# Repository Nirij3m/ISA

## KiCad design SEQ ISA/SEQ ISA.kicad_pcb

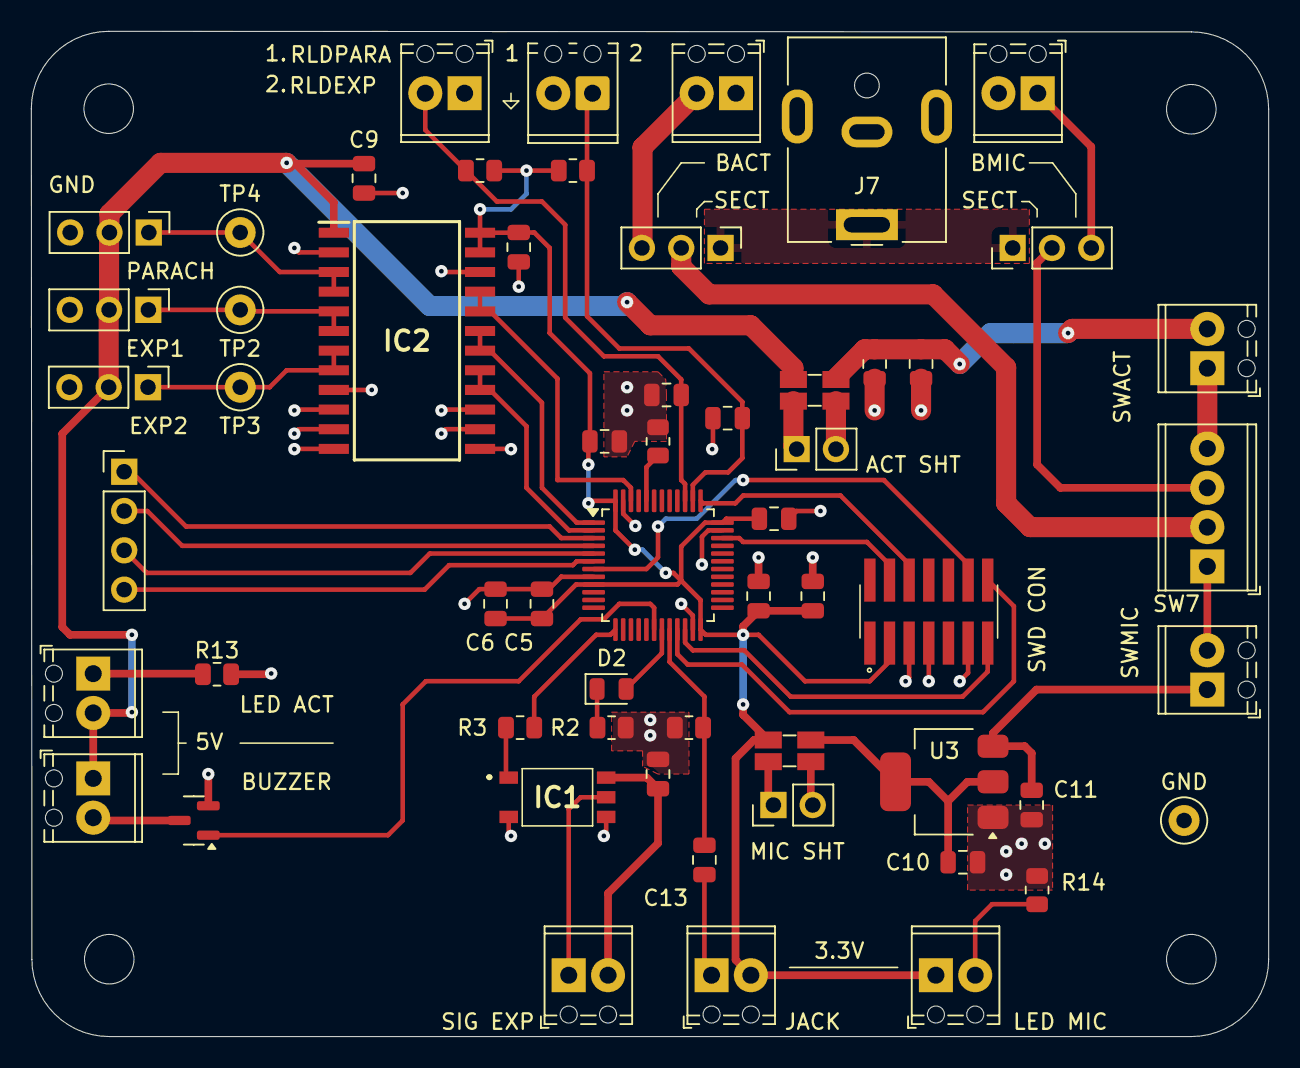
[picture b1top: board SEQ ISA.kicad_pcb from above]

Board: 2 copper layers, 80.0 x 65.0 mm, 62 parts (0 on the bottom side), 47 nets.

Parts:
ACT SHT: Conn_01x02_Pin; PinHeader_1x02_P2.54mm_Vertical
BACT: Conn_01x02_Pin; TerminalBlock_Phoenix_MPT-0,5-2-2.54_1x02_P2.54mm_Horizontal
BMIC: Conn_01x02_Pin; TerminalBlock_Phoenix_MPT-0,5-2-2.54_1x02_P2.54mm_Horizontal
BUZZER: CMI-1210-90-SMT-TR; TerminalBlock_Phoenix_MPT-0,5-2-2.54_1x02_P2.54mm_Horizontal
C1, C2, C3, C11, C16: 100n; C_0805_2012Metric
C4, C10, C12: 10u; C_0805_2012Metric
C5, C13, C22, C23: 10n; C_0805_2012Metric
C6: 1u; C_0805_2012Metric
C7, C9, C14: 0.1u; C_0805_2012Metric
D2: GREEN; LED_0805_2012Metric
EXP1, EXP2: SERVO-MOTOR; PinHeader_1x03_P2.54mm_Vertical
GND: TestPoint; TestPoint_Loop_D1.80mm_Drill1.0mm_Beaded
H1, H2, H3, H4: MountingHole; MountingHole_3.2mm_M3
IC1: TLX9310_TPL,F; TLX9310
IC2: SN74LVC4245ADW; SN74LVC4345ADW
J7: Jack-DC; BarrelJack_CUI_PJ-063AH_Horizontal
JACK: PRISE JACK; TerminalBlock_Phoenix_MPT-0,5-2-2.54_1x02_P2.54mm_Horizontal
JP1, JP2: Jumper_3_Bridged12; PinHeader_1x03_P2.54mm_Vertical
LED ACT: GREEN; TerminalBlock_Phoenix_MPT-0,5-2-2.54_1x02_P2.54mm_Horizontal
LED MIC: GREEN; TerminalBlock_Phoenix_MPT-0,5-2-2.54_1x02_P2.54mm_Horizontal
MIC SHT: Conn_01x02_Pin; PinHeader_1x02_P2.54mm_Vertical
PARACH: SERVO-MOTOR; PinHeader_1x03_P2.54mm_Vertical
PC14-15: Conn_01x04_Pin; PinHeader_1x04_P2.54mm_Vertical
Q1: BS170F; SOT-23
R2, R13, R14: 1k; R_0805_2012Metric
R3: 430; R_0805_2012Metric
R7: 10k; R_0805_2012Metric
R8, R12: R_Shunt; R_Shunt_Ohmite_LVK12
R10, R11, R15: 5.6k; R_0805_2012Metric
RLDEXP: BP1; TerminalBlock_Phoenix_MPT-0,5-2-2.54_1x02_P2.54mm_Horizontal
RLDPARA: BP2; TerminalBlock_Phoenix_MPT-0,5-2-2.54_1x02_P2.54mm_Horizontal
SIG EXP: Conn_01x02_Pin; TerminalBlock_Phoenix_MPT-0,5-2-2.54_1x02_P2.54mm_Horizontal
SW7: INTER_GENERAL; TerminalBlock_Phoenix_MPT-0,5-4-2.54_1x04_P2.54mm_Horizontal
SWACT: INTER_ACT; TerminalBlock_Phoenix_MPT-0,5-2-2.54_1x02_P2.54mm_Horizontal
SWD CON: FTSH-107-01-L-DV-K-A; FTSH-107-XX-YYY-DV-K-A
SWMIC: INTER_MIC; TerminalBlock_Phoenix_MPT-0,5-2-2.54_1x02_P2.54mm_Horizontal
TP2, TP3, TP4: TestPoint; TestPoint_Loop_D1.80mm_Drill1.0mm_Beaded
U1: STM32L010C6T6R; LQFP-48_7x7mm_P0.5mm
U3: LD1117S33TR_SOT223; SOT-223-3_TabPin2

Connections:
+3.3V: C1.1, C2.1, C3.1, C4.1, C5.1, C6.1, C7.1, IC2.23 (VCCB_(3.3_V)_1), IC2.24 (VCCB_(3.3_V)_2), JACK.2 (B), LED MIC.1 (A), R10.1, R12.4, R15.1, SWD CON.3, U1.9 (VDDA), U1.24 (VDD), U1.36 (VDD), U1.48 (VDD)
+3.3VEXP: C14.1, IC1.6 (VCC), SIG EXP.2 (Pin_1)
+5V: BUZZER.1 (+), C9.1, EXP1.2 (+), EXP2.2 (+), IC2.1 ((5_V)_VCCA), LED ACT.2 (A), PARACH.2 (+), R8.4
/BUZZER: Q1.1 (G), U1.18 (PB0)
/EXP_START: R3.1, U1.13 (PA3)
/LAUNCH_SIG: C13.2, R11.2, U1.20 (PB2)
/LED_SEQ: D2.2 (A), U1.19 (PB1)
/LPUART1_RX: SWD CON.13, U1.22 (PB11)
/LPUART1_TX: SWD CON.14, U1.21 (PB10)
/NRST: SWD CON.12, U1.7 (NRST)
/PC14: PC14-15.1 (Pin_3), U1.3 (PC14)
/PC15: PC14-15.2 (Pin_4), U1.4 (PC15)
/PH0: PC14-15.3 (Pin_1), U1.5 (PH0)
/PH1: PC14-15.4 (Pin_2), U1.6 (PH1)
/PWM1_EXP5: EXP1.1 (PWM), IC2.5 (A3), IC2.6 (A4), TP2.1
/PWM1_EXP33: IC2.18 (B4), IC2.19 (B3), U1.1 (PC0)
/PWM2_EXP5: EXP2.1 (PWM), IC2.7 (A5), IC2.8 (A6), TP3.1
/PWM2_EXP33: IC2.16 (B6), IC2.17 (B5), U1.2 (PC13)
/PWM_PARACHT5: IC2.3 (A1), IC2.4 (A2), PARACH.1 (PWM), TP4.1
/PWM_PARACHT33: IC2.20 (B2), IC2.21 (B1), U1.46 (PB9)
/RLD_EXP: C23.2, R15.2, RLDEXP.1, U1.38 (PA15)
/RLD_PARA: C22.1, R10.2, RLDPARA.2, U1.39 (PB3)
/SWD_CLK: SWD CON.6, U1.37 (PA14)
/SWD_IO: SWD CON.4, U1.34 (PA13)
GND: BACT.1, BMIC.2, C1.2, C2.2, C3.2, C4.2, C5.2, C6.2, C7.2, C9.2, C10.2, C11.2, C12.2, C14.2, C16.2, C22.2, C23.1, EXP1.3 (-), EXP2.3 (-), GND.1, IC1.3 (K), IC1.4 (GND), IC2.2 (DIR), IC2.9 (A7), IC2.10 (A8), IC2.11 (GND_1), IC2.12 (GND_2), IC2.13 (GND_3), IC2.14 (B8), IC2.15 (B7), IC2.22 (~OE), J7.2, J7.MP, PARACH.3 (-), Q1.2 (S), R2.2, R7.1, R11.1, R13.2, R14.2, RLDEXP.2, RLDPARA.1, SWD CON.5, SWD CON.7, SWD CON.11, U1.8 (VSSA), U1.23 (VSS), U1.35 (VSS), U1.47 (VSS), U3.1 (GND)
unnamed: D2.1 (K), R2.1
unnamed: LED ACT.1 (K), R13.1
unnamed: LED MIC.2 (K), R14.1
unnamed: IC1.1 (A), R3.2
unnamed: IC1.5 (VO), SIG EXP.1 (Pin_2)
unnamed: ACT SHT.1, R8.3
unnamed: ACT SHT.2, R8.2
unnamed: MIC SHT.1, R12.3
unnamed: MIC SHT.2, R12.2
unnamed: JP1.2 (C), SW7.2 (4)
unnamed: JP2.2 (C), SW7.3 (2)
unnamed: BUZZER.2 (-), Q1.3 (D)
unnamed: C13.1, JACK.1 (A)
unnamed: SW7.4 (3), SWACT.1 (A)
unnamed: C12.1, C16.1, R8.1, SWACT.2 (B)
unnamed: C11.1, SWMIC.1 (A), U3.3 (VI)
unnamed: SW7.1, SWMIC.2 (B)
unnamed: R7.2, U1.44 (BOOT0)
unnamed: C10.1, R12.1, U3.2 (VO)
VBATACT: BACT.2, JP1.3 (B)
VBATMIC: BMIC.1, JP2.3 (B)
VSECT5: J7.1, JP1.1 (A), JP2.1 (A)

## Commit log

2025-01-23 init
2025-01-23 cleanup
2025-01-23 Seq review
    added security button for launch detection, PWM motor and changd the regulator for a simpler one
2025-02-04 SEQ V2
    Added servo motor controls, trigger button security for noise sensitive input and UART com
2025-02-05 SEQ V2.1
    Added test pads and protection resistance
2025-02-11 Seq V3
2025-02-13 Started Fottprinting
2025-02-22 PCB First version
2025-02-24 Update to KicadV9 + C movement
2025-02-27 Finishing PCB
